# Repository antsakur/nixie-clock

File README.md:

# Nixie clock

ESP-IDF firmware for a four-tube HH:MM nixie clock on an ESP32-C6. The clock gets the time from SNTP over Wi-Fi, drives the tubes through shift registers, and serves a web page for setup and settings.

## Contents

- [What it does](#what-it-does)
- [How to use it](#how-to-use-it)
  - [First start](#first-start)
  - [Configuration](#configuration)
- [Functionality](#functionality)
  - [Display](#display)
    - [Clock](#clock)
    - [Cathode poisoning prevention routine](#cathode-poisoning-prevention-routine)
    - [Random digits](#random-digits)
  - [Brightness](#brightness)
  - [Presence](#presence)
  - [Time](#time)
  - [Network](#network)
- [How the hardware works](#how-the-hardware-works)
  - [Tubes](#tubes)
  - [Shift registers](#shift-registers)
  - [High-voltage supply](#high-voltage-supply)
  - [Presence sensor](#presence-sensor)
- [Build and flash](#build-and-flash)
- [Supported hardware](#supported-hardware)

## What it does

- Shows hours and minutes on four nixie tubes.
- Joins your saved Wi-Fi network and sets the clock from SNTP.
- Opens a setup network when it has no saved network, or when it cannot join.
- Can dim the tubes during night hours, and can turn the high-voltage supply off when nobody is nearby.
- Rolls the digits on a timer to reduce cathode poisoning.
- Crossfades digit changes when that effect is enabled.

Wi-Fi credentials are entered in the browser and stored on the clock.

## How to use it

### First start

1. Power the board from a 5 V supply that can provide 2 A, for example a USB phone charger. A 1 A supply may be insufficient. It opens a setup network named `NixieClock-XXXX`.
2. Join that network and open `http://nixie.local/`. If the name does not resolve, open `http://192.168.4.1/`.
3. Enter your SSID and password, then press **Join**. Tick **Hidden network** if the network is not advertised.
4. To access the configuration page, disconnect from the `NixieClock-XXXX` network, reconnect to your network, and open `http://nixie.local/` again.

### Configuration

On your network, `http://nixie.local/` opens five menus. Each **Save settings** button stores that menu on the clock, and the values stay after a reboot.

| Menu | What you can change |
|---|---|
| Display | Fade, cathode-poisoning routine, and random digits |
| Brightness | Day and night levels, night hours, and the transition between them |
| Presence | Idle timeout that turns the tubes off |
| Time | Timezone and daylight saving |
| Network | Connection details, and forgetting the saved network |

**Forget current network** on the Network page clears the saved credentials and returns the clock to the setup network.

## Functionality

The pictures are the pages from a configured clock. The values in them are that clock's saved settings, not the defaults described here.

### Display

#### Clock

The clock normally shows the current time. When fade is enabled, a digit change crossfades from the old digits to the new ones. Fade duration is how long that crossfade takes. The default is 500 ms, and it can be set from 1 ms to 5000 ms. **Test fade** fades every digit back and forth using the fade duration that is currently set. **Show clock** returns to the time.

<figure class="clip">

<figcaption><strong>All digits fading.</strong> Each tube crossfades to another digit and back, using the current fade duration.</figcaption>
</figure>

#### Cathode poisoning prevention routine

A nixie tube lights one cathode, the shaped digit, inside a gas-filled envelope. Metal slowly leaves the lit cathode and can settle on cathodes that stay dark. A clock repeats the same digits for long stretches, so unused digits grow dim, patchy, or fail to light. The routine walks every symbol on each tube so every cathode is lit regularly and that deposit does not build up.

You set the hold time for each digit, the starting offset, the run length, and whether it counts down. **Repeat every** is how many minutes pass between automatic runs. The default is 5 minutes. **Run cathode poisoning prevention routine** starts one run immediately.

<figure class="clip">

<figcaption><strong>Cathode poisoning prevention.</strong> The tubes walk through every symbol so each cathode is lit.</figcaption>
</figure>

#### Random digits

Random digits shows a changing pattern instead of the time. You set the hold time and how long the pattern runs. **Run random** starts it.

<figure class="clip">

<figcaption><strong>Random digits.</strong> The tubes show a changing pattern instead of the time.</figcaption>
</figure>

### Brightness

Tube brightness is controlled with PWM. The brightness number is the PWM duty-cycle, from 0 to 100. The defaults are 80 during the day and 60 at night. Night mode is off by default. When it is on, it runs from a start hour until an end hour and may cross midnight. The default night hours are 23:00 to 07:00. **Transition** is how many seconds the brightness takes to move between those levels, from 1 to 60. The default is 10 seconds. **Test transition** runs one change between the day and night levels.

A brightness of 0 turns the high-voltage supply off.

<figure class="clip">

<figcaption><strong>Brightness from full to off.</strong> The tubes dim from duty-cycle 100 to 0, then return to 100.</figcaption>
</figure>

### Presence

With the presence sensor enabled, the tubes turn off after the set number of minutes with nobody nearby. The default is 10 minutes. The allowed range is 1 to 240 minutes. Turning the sensor off leaves the tubes on, aside from a zero brightness setting.

### Time

Choose a timezone from the built-in list. Zones that observe daylight saving have a **Daylight saving** checkbox. The page shows the current clock time and the two SNTP servers compiled into the firmware. The defaults are `pool.ntp.org` and `time.google.com`.

The list covers UTC, the United Kingdom, Central and Eastern Europe, Finland, Moscow, India, China, Japan, Australia Eastern, and the four continental US zones.

### Network

The Network page shows the connected network, assigned IP address, firmware version, MAC address, and uptime. **Forget current network** erases the saved Wi-Fi credentials and starts the setup network again.

## How the hardware works

The clock is two boards. The lower board makes 170 V from the 5 V input and carries the presence sensor. The upper board holds four IN-14 nixie tubes and the shift registers that select their digits. An ESP32-C6 development kit is the controller. It gets the time over Wi-Fi and drives the shift registers, the tube brightness, and the high-voltage enable pin.

The high-voltage wiring can sit at 170 V while the clock is on. Do not touch that circuitry while it is powered.

### Tubes

Each IN-14 is a gas-filled tube with one common anode and a separate cathode for every symbol. About 170 V between the anode and a cathode ionizes the gas, and the glow takes the shape of that cathode. After the tube has struck, it keeps glowing at a lower voltage, about 145 V. The tube then looks like a short circuit, so each anode has a 13 kΩ resistor that holds the digit current to a few milliamps.

Each tube has cathodes for digits 0–9 and for a left and a right decimal point.

### Shift registers

Six TPIC6B595 shift registers are chained together. Each one has eight open-drain outputs that can pull a cathode to ground. An output that is on lights that cathode. An output that is off leaves it dark. The chain is 48 bits, sent least significant bit first:

| Bits | Tube |
|---|---|
| 47–36 | Hour tens |
| 35–24 | Hour ones |
| 23–12 | Minute tens |
| 11–0 | Minute ones |

Each group of 12 bits is one tube, in this order: left dot, digits 1 through 9, digit 0, right dot.

The controller sends serial data and a clock, then pulses the latch so all six registers update together. Output enable is a PWM signal. Its duty-cycle is the brightness number on the configuration page. The shift registers run from 5 V. Their outputs are clamped so they can sit at the tube voltage when a cathode is off.

### High-voltage supply

A flyback converter raises 5 V to 170 V for the tube anodes. An LT3757 controls the switch. The transformer is a Würth 750032051, with a 1:10 turns ratio so the switch duty-cycle stays in a practical range at 200 kHz. A BSC059N04LS6 MOSFET switches the primary. A VS-3EMH06 diode rectifies the secondary. An RCD snubber clamps the voltage spike on the MOSFET when it turns off. The converter is designed for about 20 mA at 170 V, which is enough for the four tubes. One GPIO enables the converter. Turning that pin off removes the anode voltage and the tubes go dark.

### Presence sensor

An HLK-LD2420 24 GHz radar module watches for a person nearby. It was chosen instead of a passive infrared sensor because it still sees someone who is sitting still. The clock only uses the module's presence output. A high level means someone is nearby, and a low level means the area is empty. When that output stays empty for the configured number of minutes, the firmware turns the high-voltage supply off.

## Build and flash

You need ESP-IDF 6.x. The target is `esp32c6`.

```bash
idf.py set-target esp32c6
idf.py menuconfig   # User Configuration: board and SNTP servers
idf.py build
idf.py -p /dev/ttyUSB0 flash monitor
```

In **User Configuration**:

- **Board** selects the DevKit pin map. The default is `ESP32_C6_WROOM_1`.
- **SNTP server** and **Backup SNTP server** are the only time servers the clock uses.
- **Initial connection retry count** is how many station disconnects to tolerate before giving up on credentials that have not yet received an IP, and before bringing the setup network back after a later disconnect. The default is 5.

Flash through the USB-UART bridge. The commands above use `/dev/ttyUSB0`.

## Supported hardware

| Board | Module | menuconfig |
|---|---|---|
| ESP32-C6-DevKitC-1 | ESP32-C6-WROOM-1 | `ESP32_C6_WROOM_1` (default) |
| ESP32-C6-DevKitM-1 | ESP32-C6-MINI-1 | `ESP32_C6_MINI_1` |

The firmware also expects:

- Four nixie tubes driven by shift registers (latch, data, and clock).
- A high-voltage supply with an enable pin.
- A PWM output-enable line for tube brightness.
- A presence sensor input.

Choosing the wrong board in menuconfig drives the high-voltage enable and the shift-register pins on the wrong GPIOs. The pin map for both kits is in [docs/esp32-c6-devkits.md](docs/esp32-c6-devkits.md).

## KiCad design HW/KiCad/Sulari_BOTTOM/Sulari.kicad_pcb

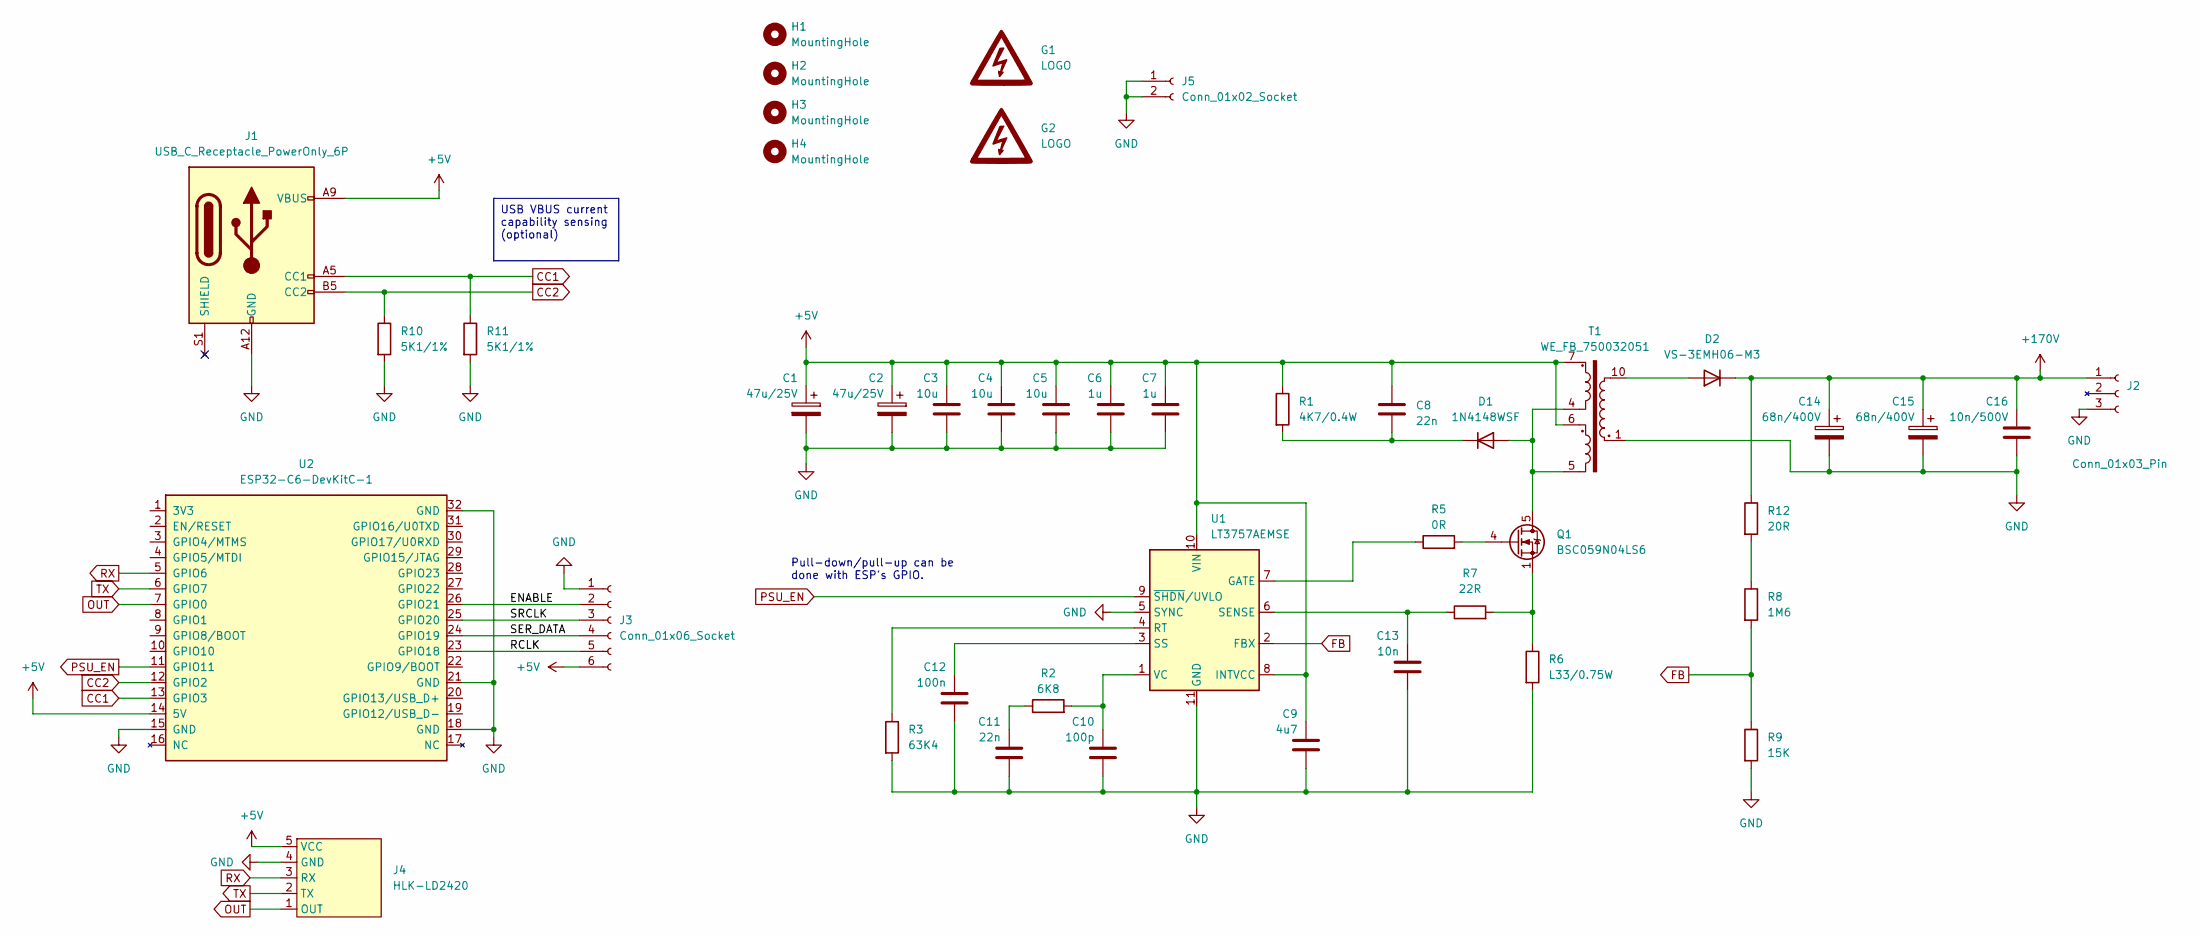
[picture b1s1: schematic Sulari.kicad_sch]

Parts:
C1, C2: 47u/25V; CP_Radial_D8.0mm_P3.50mm
C3, C4, C5: 10u; C_1206_3216Metric
C6, C7: 1u; C_0805_2012Metric
C8, C11: 22n; C_0603_1608Metric
C9: 4u7; C_0805_2012Metric
C10: 100p; C_0603_1608Metric
C12: 100n; C_0603_1608Metric
C13: 10n; C_0603_1608Metric
C14, C15: 68n/400V; C_Rect_L10.3mm_W5.0mm_P7.50mm_MKS4
C16: 10n/500V; C_1206_3216Metric_Pad1.33x1.80mm_HandSolder
D1: 1N4148WSF; D_SOD-323F
D2: VS-3EMH06-M3; D_SMA
G1, G2: LOGO; HIGH_VOLTAGE_LOGO
H1, H2, H3, H4: MountingHole; MountingHole_3.2mm_M3_Pad_Via
J1: USB_C_Receptacle_PowerOnly_6P; USB_C_Receptacle_GCT_USB4125-xx-x-0190_6P_TopMnt_Horizontal
J2: Conn_01x03_Pin; PinSocket_1x03_P2.54mm_Vertical
J3: Conn_01x06_Socket; PinSocket_1x06_P2.54mm_Vertical
J4: HLK-LD2420; Molex_PicoBlade_53048-0510_1x05_P1.25mm_Horizontal
J5: Conn_01x02_Socket; PinSocket_1x02_P2.54mm_Vertical
Q1: BSC059N04LS6; PG-TDSON-8-FL_correct
R1: 4K7/0.4W; R_0805_2012Metric
R2: 6K8; R_0603_1608Metric
R3: 63K4; R_0603_1608Metric
R5: 0R; R_0805_2012Metric_Pad1.20x1.40mm_HandSolder
R6: L33/0.75W; R_0805_2012Metric
R7: 22R; R_0603_1608Metric
R8: 1M6; R_1206_3216Metric
R9: 15K; R_0603_1608Metric
R10, R11: 5K1/1%; R_0805_2012Metric
R12: 20R; R_1206_3216Metric_Pad1.30x1.75mm_HandSolder
T1: WE_FB_750032051; WE_FB 750032051
U1: LT3757AEMSE; MSOP-10-1EP_3x3mm_P0.5mm_EP1.68x1.88mm_ThermalVias
U2: ESP32-C6-DevKitC-1

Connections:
+5V: C1.1, C2.1, C3.1, C4.1, C5.1, C6.1, C7.1, C8.1, C9.1, J1.A9 (VBUS), J1.B9 (VBUS), J3.6, J4.5 (VCC), R1.1, T1.6, T1.7, U1.8 (INTVCC), U1.10 (VIN), U2.14 (5V)
+170V: C14.1, C15.1, C16.1, D2.1 (K), J2.1, R12.1
/ENABLE: J3.2, U2.26 (GPIO21)
/RCLK: J3.5, U2.23 (GPIO18)
/SER_DATA: J3.4, U2.24 (GPIO19)
/SRCLK: J3.3, U2.25 (GPIO20)
CC1: J1.A5 (CC1), R11.1, U2.13 (GPIO3)
CC2: J1.B5 (CC2), R10.1, U2.12 (GPIO2)
FB: R8.2, R9.1, U1.2 (FBX)
GND: C1.2, C2.2, C3.2, C4.2, C5.2, C6.2, C7.2, C9.2, C10.2, C11.2, C12.2, C13.2, C14.2, C15.2, C16.2, J1.A12 (GND), J1.B12 (GND), J2.3, J3.1, J4.4 (GND), J5.1, J5.2, R3.2, R6.2, R9.2, R10.2, R11.2, T1.1, U1.5 (SYNC), U1.11 (GND), U2.15 (GND), U2.18 (GND), U2.21 (GND), U2.32 (GND)
unnamed: C11.1, R2.1
unnamed: D1.2 (A), Q1.5 (D), T1.4, T1.5
unnamed: C8.2, D1.1 (K), R1.2
unnamed: D2.2 (A), T1.10
unnamed: Q1.4 (G), R5.2
unnamed: Q1.1 (S), R6.1, R7.2
unnamed: R8.1, R12.2
unnamed: R5.1, U1.7 (GATE)
unnamed: R3.1, U1.4 (RT)
unnamed: C13.1, R7.1, U1.6 (SENSE)
unnamed: C12.1, U1.3 (SS)
unnamed: C10.1, R2.2, U1.1 (VC)
OUT: J4.1 (OUT), U2.7 (GPIO0)
PSU_EN: U1.9 (~SHDN/UVLO), U2.11 (GPIO11)
RX: J4.3 (RX), U2.5 (GPIO6)
TX: J4.2 (TX), U2.6 (GPIO7)

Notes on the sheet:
USB VBUS current capability sensing (optional)
Pull-down/pull-up can be done with ESP's GPIO.

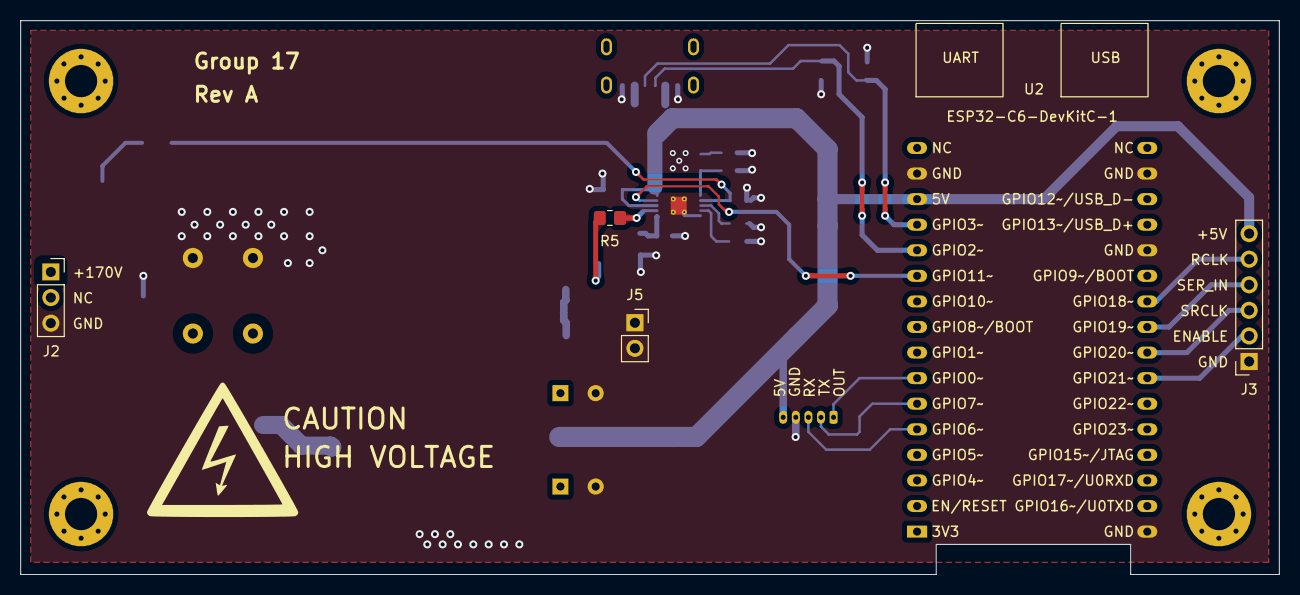
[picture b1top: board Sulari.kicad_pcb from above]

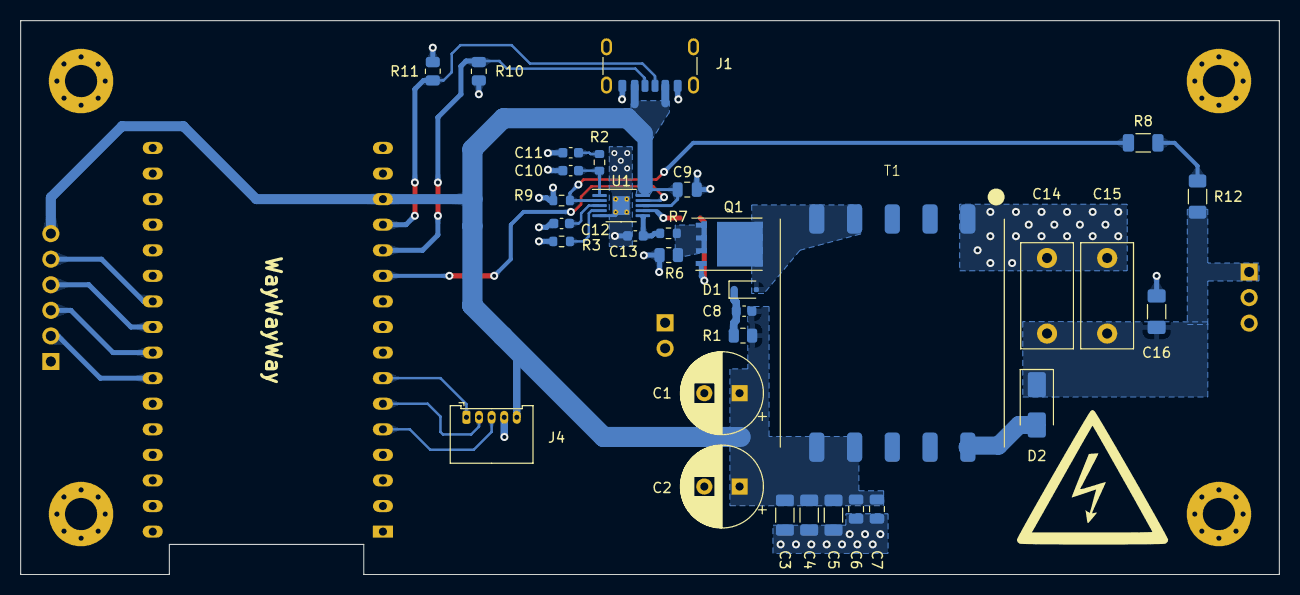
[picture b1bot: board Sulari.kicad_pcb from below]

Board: 2 copper layers, 125.0 x 55.0 mm, 44 parts (34 on the bottom side), 26 nets.

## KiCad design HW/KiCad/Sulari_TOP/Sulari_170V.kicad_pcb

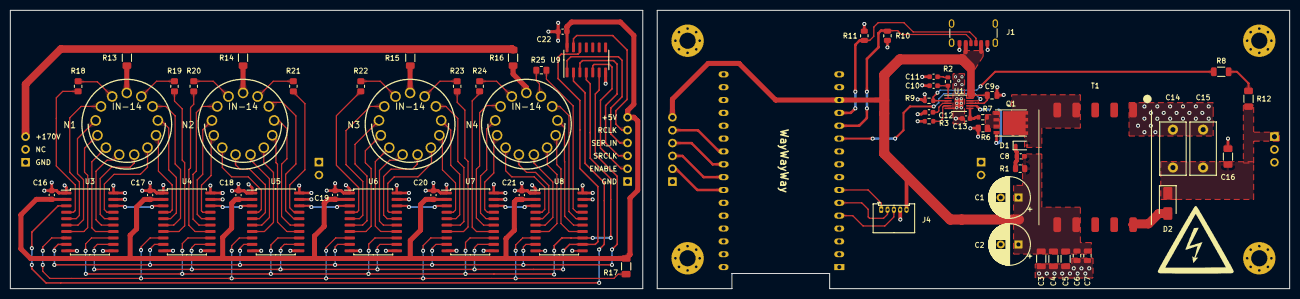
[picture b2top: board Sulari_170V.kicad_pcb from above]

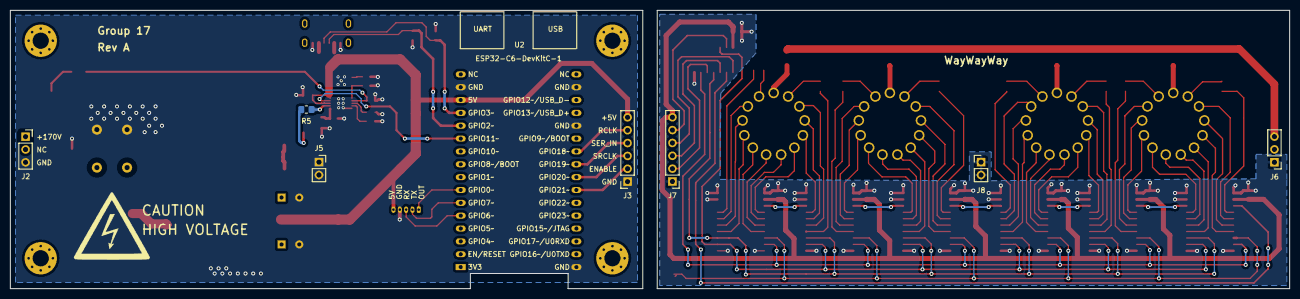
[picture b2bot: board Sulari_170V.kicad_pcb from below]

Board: 2 copper layers, 252.9 x 55.0 mm, 78 parts (13 on the bottom side), 101 nets.

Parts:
C1, C2: 47u/25V; CP_Radial_D8.0mm_P3.50mm
C3, C4, C5: 10u; C_1206_3216Metric
C6, C7: 1u; C_0805_2012Metric
C8, C11: 22n; C_0603_1608Metric
C9: 4u7; C_0805_2012Metric
C10: 100p; C_0603_1608Metric
C12: 100n; C_0603_1608Metric
C13: 10n; C_0603_1608Metric
C14, C15: 68n/400V; C_Rect_L10.3mm_W5.0mm_P7.50mm_MKS4
C16, C17, C18, C19, C20, C21, C22: 100n; C_0603_1608Metric_Pad1.08x0.95mm_HandSolder
C16#2: 10n/500V; C_1206_3216Metric_Pad1.33x1.80mm_HandSolder
D1: 1N4148WSF; D_SOD-323F
D2: VS-3EMH06-M3; D_SMA
G1, G2: LOGO; HIGH_VOLTAGE_LOGO
H1, H2, H3, H4: MountingHole; MountingHole_3.2mm_M3_Pad_Via
J1: USB_C_Receptacle_PowerOnly_6P; USB_C_Receptacle_GCT_USB4125-xx-x-0190_6P_TopMnt_Horizontal
J2: Conn_01x03_Pin; PinSocket_1x03_P2.54mm_Vertical
J3: Conn_01x06_Socket; PinSocket_1x06_P2.54mm_Vertical
J4: HLK-LD2420; Molex_PicoBlade_53048-0510_1x05_P1.25mm_Horizontal
J5: Conn_01x02_Socket; PinSocket_1x02_P2.54mm_Vertical
J6: Conn_01x03; PinHeader_1x03_P2.54mm_Vertical
J7: Conn_01x06; PinHeader_1x06_P2.54mm_Vertical
J8: Conn_01x02; PinHeader_1x02_P2.54mm_Vertical
N1, N2, N3, N4: IN-14; nixies-us-IN-14-socket
Q1: BSC059N04LS6; PG-TDSON-8-FL
R1: 4K7/0.4W; R_0805_2012Metric
R2: 6K8; R_0603_1608Metric
R3: 63K4; R_0603_1608Metric
R5: 0R; R_0805_2012Metric_Pad1.20x1.40mm_HandSolder
R6: L33/0.75W; R_0805_2012Metric
R7: 22R; R_0603_1608Metric
R8: 1M6; R_1206_3216Metric
R9: 15K; R_0603_1608Metric
R10, R11: 5K1/1%; R_0805_2012Metric
R12: 20R; R_1206_3216Metric_Pad1.30x1.75mm_HandSolder
R13, R14, R15, R16, R17: 13K; R_1206_3216Metric_Pad1.30x1.75mm_HandSolder
R18, R19, R20, R21, R22, R23, R24, R25: 100k; R_0805_2012Metric_Pad1.20x1.40mm_HandSolder
T1: WE_FB_750032051; WE_FB 750032051
U1: LT3757AEMSE; MSOP-10-1EP_3x3mm_P0.5mm_EP1.68x1.88mm
U2: ESP32-C6-DevKitC-1
U3, U4, U5, U6, U7, U8: TPIC6B595; SOIC-20W_7.5x12.8mm_P1.27mm
U9: SN74HCT04, 6-ch 5V logic inverter; SOIC-14_3.9x8.7mm_P1.27mm

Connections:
+5V: C1.1, C2.1, C3.1, C4.1, C5.1, C6.1, C7.1, C8.1, C9.1, C16.1, C17.1, C18.1, C19.1, C20.1, C21.1, C22.1, J1.A9 (VBUS), J1.B9 (VBUS), J3.6, J4.5 (VCC), J7.6, R1.1, R17.1, T1.6, T1.7, U1.8 (INTVCC), U1.10 (VIN), U2.14 (5V), U3.2 (VCC), U4.2 (VCC), U5.2 (VCC), U6.2 (VCC), U7.2 (VCC), U8.2 (VCC), U9.14
+170V: C14.1, C15.1, C16#2.1, D2.1 (K), J2.1, R12.1
/ENABLE: J3.2, U2.26 (GPIO21)
/RCLK: J3.5, U2.23 (GPIO18)
/SER_DATA: J3.4, U2.24 (GPIO19)
/SRCLK: J3.3, U2.25 (GPIO20)
/VDD_170V: J6.3, R13.1, R14.1, R15.1, R16.1
/~SRCLR: R17.2, U3.8 (~SRCLR), U4.8 (~SRCLR), U5.8 (~SRCLR), U6.8 (~SRCLR), U7.8 (~SRCLR), U8.8 (~SRCLR)
CC1: J1.A5 (CC1), R11.1, U2.13 (GPIO3)
CC2: J1.B5 (CC2), R10.1, U2.12 (GPIO2)
ENABLE: J7.2, U9.5
FB: R8.2, R9.1, U1.2 (FBX)
GND: C1.2, C2.2, C3.2, C4.2, C5.2, C6.2, C7.2, C9.2, C10.2, C11.2, C12.2, C13.2, C14.2, C15.2, C16.2, C16#2.2, C17.2, C18.2, C19.2, C20.2, C21.2, C22.2, J1.A12 (GND), J1.B12 (GND), J2.3, J3.1, J4.4 (GND), J5.1, J5.2, J6.1, J7.1, J8.1, J8.2, R3.2, R6.2, R9.2, R10.2, R11.2, T1.1, U1.5 (SYNC), U1.11 (GND), U2.15 (GND), U2.18 (GND), U2.21 (GND), U2.32 (GND), U3.1 (PGND), U3.10 (PGND), U3.11 (PGND), U3.19 (LGND), U3.20 (PGND), U4.1 (PGND), U4.10 (PGND), U4.11 (PGND), U4.19 (LGND), U4.20 (PGND), U5.1 (PGND), U5.10 (PGND), U5.11 (PGND), U5.19 (LGND), U5.20 (PGND), U6.1 (PGND), U6.10 (PGND), U6.11 (PGND), U6.19 (LGND), U6.20 (PGND), U7.1 (PGND), U7.10 (PGND), U7.11 (PGND), U7.19 (LGND), U7.20 (PGND), U8.1 (PGND), U8.10 (PGND), U8.11 (PGND), U8.19 (LGND), U8.20 (PGND), U9.7
unnamed: C11.1, R2.1
unnamed: D1.2 (A), Q1.5 (D), T1.4, T1.5
unnamed: C8.2, D1.1 (K), R1.2
unnamed: D2.2 (A), T1.10
unnamed: N1.A, R13.2
unnamed: N1.LHDP, R18.2
unnamed: N1.RHDP, R19.1
unnamed: N2.A, R14.2
unnamed: N2.LHDP, R20.2
unnamed: N2.RHDP, R21.1
unnamed: N3.A, R15.2
unnamed: N3.LHDP, R22.2
unnamed: N3.RHDP, R23.1
unnamed: N4.A, R16.2
unnamed: N4.LHDP, R24.2
unnamed: N4.RHDP, R25.1
unnamed: Q1.4 (G), R5.2
unnamed: Q1.1 (S), R6.1, R7.2
unnamed: R8.1, R12.2
unnamed: R5.1, U1.7 (GATE)
unnamed: R3.1, U1.4 (RT)
unnamed: C13.1, R7.1, U1.6 (SENSE)
unnamed: C12.1, U1.3 (SS)
unnamed: C10.1, R2.2, U1.1 (VC)
unnamed: R18.1, U3.4 (DRAIN0)
unnamed: N1.1, U3.5 (DRAIN1)
unnamed: N1.2, U3.6 (DRAIN2)
unnamed: N1.3, U3.7 (DRAIN3)
unnamed: N1.4, U3.14 (DRAIN4)
unnamed: N1.5, U3.15 (DRAIN5)
unnamed: N1.6, U3.16 (DRAIN6)
unnamed: N1.7, U3.17 (DRAIN7)
unnamed: U3.18 (SER_OUT), U4.3 (SER_IN)
unnamed: N1.8, U4.4 (DRAIN0)
unnamed: N1.9, U4.5 (DRAIN1)
unnamed: N1.0, U4.6 (DRAIN2)
unnamed: R19.2, U4.7 (DRAIN3)
unnamed: R20.1, U4.14 (DRAIN4)
unnamed: N2.1, U4.15 (DRAIN5)
unnamed: N2.2, U4.16 (DRAIN6)
unnamed: N2.3, U4.17 (DRAIN7)
unnamed: U4.18 (SER_OUT), U5.3 (SER_IN)
unnamed: N2.4, U5.4 (DRAIN0)
unnamed: N2.5, U5.5 (DRAIN1)
unnamed: N2.6, U5.6 (DRAIN2)
unnamed: N2.7, U5.7 (DRAIN3)
unnamed: N2.8, U5.14 (DRAIN4)
unnamed: N2.9, U5.15 (DRAIN5)
unnamed: N2.0, U5.16 (DRAIN6)
unnamed: R21.2, U5.17 (DRAIN7)
unnamed: U5.18 (SER_OUT), U6.3 (SER_IN)
unnamed: R22.1, U6.4 (DRAIN0)
unnamed: N3.1, U6.5 (DRAIN1)
unnamed: N3.2, U6.6 (DRAIN2)
unnamed: N3.3, U6.7 (DRAIN3)
unnamed: N3.4, U6.14 (DRAIN4)
unnamed: N3.5, U6.15 (DRAIN5)
unnamed: N3.6, U6.16 (DRAIN6)
unnamed: N3.7, U6.17 (DRAIN7)
unnamed: U6.18 (SER_OUT), U7.3 (SER_IN)
unnamed: N3.8, U7.4 (DRAIN0)
unnamed: N3.9, U7.5 (DRAIN1)
unnamed: N3.0, U7.6 (DRAIN2)
unnamed: R23.2, U7.7 (DRAIN3)
unnamed: R24.1, U7.14 (DRAIN4)
unnamed: N4.1, U7.15 (DRAIN5)
unnamed: N4.2, U7.16 (DRAIN6)
unnamed: N4.3, U7.17 (DRAIN7)
unnamed: U7.18 (SER_OUT), U8.3 (SER_IN)
unnamed: N4.4, U8.4 (DRAIN0)
unnamed: N4.5, U8.5 (DRAIN1)
unnamed: N4.6, U8.6 (DRAIN2)
unnamed: N4.7, U8.7 (DRAIN3)
unnamed: N4.8, U8.14 (DRAIN4)
unnamed: N4.9, U8.15 (DRAIN5)
unnamed: N4.0, U8.16 (DRAIN6)
unnamed: R25.2, U8.17 (DRAIN7)
OUT: J4.1 (OUT), U2.7 (GPIO0)
PSU_EN: U1.9 (~SHDN/UVLO), U2.11 (GPIO11)
RCLK: J7.5, U9.13
RX: J4.3 (RX), U2.5 (GPIO6)
SER_IN: J7.4, U9.1
SRCLK: J7.3, U9.3
TX: J4.2 (TX), U2.6 (GPIO7)
~ENABLE: U3.9 (~G), U4.9 (~G), U5.9 (~G), U6.9 (~G), U7.9 (~G), U8.9 (~G), U9.6
~RCLK: U3.12 (RCLK), U4.12 (RCLK), U5.12 (RCLK), U6.12 (RCLK), U7.12 (RCLK), U8.12 (RCLK), U9.12
~SER_IN: U3.3 (SER_IN), U9.2
~SRCLK: U3.13 (SRCK), U4.13 (SRCK), U5.13 (SRCK), U6.13 (SRCK), U7.13 (SRCK), U8.13 (SRCK), U9.4

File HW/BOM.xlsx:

Item # | Qty |  | Ref Des | Manufacturer | Manf part num | Description | Footprint | Type | Digikey price/pc (€) | Total
 |  | Comment
 |  | Capacitors |  |  |  |  |  |  | excluding VAT
 | 1 | 100pF | C10 | Yageo | CC0603JRNPO9BN101 | Multilayer Ceramic Capacitor, 100 pF, 50 V, ± 5%, C0G (NP0), 0603 [1608 Metric] | 0603 | SMT | 0.09 | 0.09
 | 1 | 10nf, 500V, X7R | C16 | Wurth Elektronik | 885342208009 | Cap Cer 10000PF 500V X7R 1206 | 1206 | SMT | 0.12 | 0.12
 | 1 | 10nf | C13 | Murata | GCM188R72A103KA37D | Multilayer Ceramic Capacitor, 0.01 uF, 100 V, ± 10%, X7R, 0603 [1608 Metric] | 0603 | SMT | 0.09 | 0.09
 | 2 | 22nf, 100V | C8,C11 | Murata | GCM188R72A223KA37J | Multilayer Ceramic Capacitor, 0.022 uF, 100 V, ± 10%, X7R, 0603 [1608 Metric] | 0603 | SMT | 0.1 | 0.2
 | 2 | 68nf, 400V | C14, C15 | Wurth Elektronik | 890283422001CS | Cap, 0.068Uf, 400V, Film, Radial Rohs Compliant: Yes |Wurth Elektronik 89028342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 | WCAP-FTBE_L10.5xH11xP7.5 | THT | 0.44 | 0.88
 | 7 | 100nf, 16V | C12, C17-22 | Yageo | CC0603KRX7R7BB104 | Multilayer Ceramic Capacitor, 0.1 uF, 16 V, ± 10%, X7R, 0603 [1608 Metric] | 0603 | SMT | 3.9E-2 | 0.27300000000000002
 | 2 | 1uf, 25V, X7R | C6,C7 | Samsung | CL21B105KAFNNNE | Multilayer Ceramic Capacitor, 1 uF, 25 V, ± 10%, X7R, 0805 [2012 Metric] | 0805 | SMT | 0.09 | 0.18
 | 3 | 10uf, 25V, X7R | C3,C4,C5 | Samsung | CL31B106KAHNFNE | Multilayer Ceramic Capacitor, 10 uF, 25 V, ± 10%, X7R, 1206 [3216 Metric] | 1206 | SMT | 0.21 | 0.63
 | 1 | 47uF, 16V, X7R | C9 | Murata | GRM21BR71C475KE51L | Multilayer Ceramic Capacitor, 4.7 uF, 16 V, ± 10%, X7R, 0805 [2012 Metric] | 0805 | SMT | 0.14000000000000001 | 0.14000000000000001
 | 2 | 47uF, 25V | C1,C2 | Wurth Elektronik | 870025574002 | WCAP-PTG5 Aluminum Polymer Capacitors | WCAP-PTG5_D8xH8xP3.5 | THT | 0.68 | 1.36
 | 1 | 0 | R5 | Yageo | RC0805FR-070RL | Thick film chip resistor; smd; 0805; 0.00R; 0.125W; 1%; ; operating temperature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 | 0805 | SMT | 0.09 | 0.09
 | 1 | 2 | R5 | Yageo | RC0805FR-072RL | SMD Chip Resistor, 2 Ohm, ± 1%, 125 mW, 0805 [2012 Metric], Thick Film, General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 | 0805 | SMT | 0.09 | 0.09
 | 1 | 33m, 3/4W | R6 | Thin Film Tech | D1WEL0805MR033F-T5 | Res 0.033 Ohm 1% 3/4W 0805 | 0805 | SMT | 0.42 | 0.42
 | 1 | 20 | R12 | Yageo | RC1206JR-0720RL | SMD Chip Resistor, 20 Ohm, ± 5%, 250 mW, 1206 [3216 Metric], Thick Film, Genera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 | 1206 | SMT | 0.09 | 0.09
 | 1 | 22 | R7 | Yageo | RC0603FR0722RL | SMD Chip Resistor, 22 Ohm, ± 1%, 100 mW, 0603 [1608 Metric], Thick Film, Genera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 | 0603 | SMT | 0.09 | 0.09
 | 1 | 4.7k, 0.4W | R1 | Vishay | RCS08054K70FKEA | Res Thick Film 0805 4.7K Ohm 1% 0.4W ±100ppm/°C Pad SMD Automotive Medical T/R | 0805 | SMT | 0.12 | 0.12
 | 2 | 5.1k, 1% | R10,R11 | Yageo | RC0805FR-075K1L | SMD Chip Resistor, 5.1 kOhm, ± 1%, 125 mW, 0805 [2012 Metric], Thick Film, Gene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 | 0805 | SMT | 0.09 | 0.18
 | 1 | 6.8k | R2 | Yageo | RC0603FR-076K8L | SMD Chip Resistor, 6.8 kOhm, ± 1%, 100 mW, 0603 [1608 Metric], Thick Film, Gene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 | 0603 | SMT | 0.09 | 0.09
 | 5 | 13k | R13-17 | KOA Speer | RK73B2BTTD133J | Res Thick Film 1206 13K Ohm 5% 0.25W(1/4W) ±200ppm/C Pad SMD Automotive T/R | 1206 | SMT | 0.03 | 0.15
 | 1 | 15k | R9 | Yageo | RC0603FR-0715KL | SMD Chip Resistor, 15 kOhm, ± 1%, 100 mW, 0603 [1608 Metric], Thick Film, Gener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 | 0603 | SMT | 0.09 | 0.09
 | 1 | 63.4k | R3 | Stackpole Electronics | RMCF0603FT63K4 | Res Thick Film 0603 63.4K Ohm 1% 1/10W ±100ppm/°C Molded SMD SMD Paper T/R | 0603 | SMT | 0.09 | 0.09
 | 8 | 100k | R18-R25 | Yageo | RC0805FR-07100KL |  | 0805 | SMT
 | 1 | 1.6M | R8 | Yageo | RC1206FR-071M6L | SMD Chip Resistor, 1.6 MOhm, ± 1%, 250 mW, 1206 [3216 Metric], Thick Film, Gene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 | 1206 | SMT | 0.09 | 0.09
 | 1 | 2A, 600V | D2 | Vishay | VS-3EMH06-M3/5AT | Diode Hyper Fast Recovery Rectifier 600V 3A 2-Pin DO-214AC Plastic T/R | SMA (DO-214AC) | SMT | 0.4 | 0.4
 | 1 | 0.25A, 100V | D1 | Diodes Inc. | 1N4148WSF-7 | Rectifier Diode Small Signal Switching 100V 0.25A 4ns 2-Pin SOD-323F T/R | SOD323F | SMT | 0.17 | 0.17
 | 1 | 40V | Q1 | Infineon | BSC059N04LS6 | OptiMO 6 40V power MOSFETs combining best-in-class RDS(on) with superior switch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 | TDSON-8 FL | SMT | 1.05 | 1.05
 | 1 | 10uH | T1 | Wurth Elektronik | 750032051 | Pulse Transformer, 1: 10, 10 H, 0.7 Ohm, 1 Kv | - | SMT | 4.68 | 4.68
 | 1 | LT3757A | U1 | Analog Devices | LT3757AEMSE#PBF | DC DC Cntrlr Single-OUT Flyback Controller 2.9V to 40V Input Automotive 10-Pin 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 | 10-TFSOP, 10-MSOP (0.118", 3.00mm Width) Exposed Pad | SMT | 6.15 | 6.15
 | 6 | TPIC6B595 | U3-U8 | Texas Instruments | TPIC6B595DWR | 8 Bit Sipo Shift Register, SOIC-20; Shif; Msl: Msl 1 - Unlimited; Svhc: No Svhc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 | 20-SOIC | SMT | 1.39 | 8.34
 | 1 | SN74HCT04 | U9 | Texas Instruments | SN74HCT04DR | 6-ch, 4.5-V to 5.5-V inverters with TTL-compatible CMOS inputs 14-SOIC -40 to 85 | 14-SOIC | SMT | 0.33 | 0.33
 | 1 | USB4125 | J1 | GCT | USB4125-GF-A-0190 | 24 (6+18 Dummy) Position USB-C (USB TYPE-C) USB 2.0 Receptacle Connector | USB 6P | THT | 0.62 | 0.62
 | 1 | 5POS 1.25mm | J4 | Molex | 0530480510 | Conn Shrouded Header (4 Sides) HDR 5 POS 1.25mm Solder RA Side Entry Thru-Hole 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 | 1x05_P1.25mm | THT | 0.45 | 0.45
 | 1 | 5POS 1.25mm | - | Molex | 0510210500 | MOLEX 51021-0500 1.25mm Pitch Housing Female 5p PicoBlade Wire-to-Wire +Wire-to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 | - | CONNECTOR | 0.24 | 0.24
 | 10 | 28-32AWG | - | Molex | 0500588000 | 1.25mm Pitch, PicoBlade Female Crimp Terminal, Tin (Sn) Plating, 28-32 AWG, Reel | - | CONNECTOR | 3.9E-2 | 0.39
 | 1 | 2POS socket | J5 | Sullins | PPPC021LFBN-RC | Female, 2 C, Straight .100" CC; 3.20mm Tail, No Mounting; PBT, Phos. Bronze, 10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 | 1x02_P2.54mm | THT | 0.31 | 0.31
 | 1 | 3POS socket | J2 | Sullins | PPPC031LFBN-RC | 3 Position Total Single Row 2.54 mm Pitch Straight Female Header | 1x03_P2.54mm | THT | 0.35 | 0.35
 | 1 | 6POS socket | J3 | Sullins | PPPC061LFBN-RC | 6 Position Header Connector 0.100 (2.54mm) Through Hole Gold" | 1x06_P2.54mm | THT | 0.5 | 0.5
 | 1 | 2POS header | J8 | Sullins | PREC002SAAN-RC | Automotive Connectors CLIP HSG FOR 090 II MLC | 1x02_P2.54mm | THT | 0.09 | 0.09
 | 1 | 3POS header | J6 | Sullins | PREC003SAAN-RC | Conn Header Vert 3POS 2.54MM | 1x03_P2.54mm | THT | 0.09 | 0.09
 | 1 | 6POS header | J7 | Sullins | PREC006SAAN-RC | Conn Header .100" Sngl Str 6POS | 1x06_P2.54mm | THT | 0.14000000000000001 | 0.14000000000000001
 | 60 | Tube socket |  | Preci-Dip | 01401-87-3010 | Pin Receptacle Connector 0.014" |  | THT | 8.7300000000000003E-2 | 5.2380000000000004
 | 1 | ESP32-C6 | U2 | Espressif | ESP32-C6-DEVKITC-1-N8 | Development Board WiFi, Bluetooth® 5, Flash 8MB | 2x15_P2.54mm | THT | 8.31 | 8.31
 | 2 | 15POS socket |  | Sullins | PPTC151LFBN-RC | Board Connector, 15 Contact(s), 1 Row(s), Female, Straight, 0.1 inch Pitch, Sol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 | 2x15_P2.54mm | THT | 0.91 | 1.82
 | 4 | 970150321 |  | Wurth Elektronik | 970150321 | WA-SSTII Steel Spacer Stud Metric Thread int./int. | M3x0.5 15mm |  | 0.34 | 1.36
 | 4 | 50M030050P008 |  | Essentra | 50M030050P008 | Pan Phillips Screw, M3 X .5 Thread, 8MM Lg | Essentra Components 50M030050P008 | M3x0.5 8mm |  | 0.12 | 0.48
 |  |  |  |  |  |  |  |  | Total w/o VAT | 45.221000000000004
 |  |  |  |  |  |  |  |  | TOTAL VAT 24% | 56.074040000000004

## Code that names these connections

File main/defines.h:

#if CONFIG_ESP32_C6_WROOM_1
    #define GPIO_PRESENCE_SENSOR GPIO_NUM_0
    #define GPIO_VBUS_CC2        GPIO_NUM_1
    #define GPIO_VBUS_CC1        GPIO_NUM_2
    #define GPIO_UART_RX         GPIO_NUM_6
    #define GPIO_UART_TX         GPIO_NUM_7
    #define GPIO_PSU_EN          GPIO_NUM_11
    #define GPIO_RCLK            GPIO_NUM_18
    #define GPIO_SRDATA          GPIO_NUM_19
    #define GPIO_SRCLK           GPIO_NUM_20
    #define GPIO_OUTPUT_EN       GPIO_NUM_21
#elif CONFIG_ESP32_C6_MINI_1
    #define GPIO_PRESENCE_SENSOR GPIO_NUM_0
    //#define GPIO_VBUS_CC2        GPIO_NUM_
    //#define GPIO_VBUS_CC1        GPIO_NUM_
    #define GPIO_UART_RX         GPIO_NUM_4
    #define GPIO_UART_TX         GPIO_NUM_5
    #define GPIO_PSU_EN          GPIO_NUM_7
    #define GPIO_RCLK            GPIO_NUM_15
    #define GPIO_SRDATA          GPIO_NUM_18
    #define GPIO_SRCLK           GPIO_NUM_19
    #define GPIO_OUTPUT_EN       GPIO_NUM_20
#endif

#define RMT_RESOLUTION_HZ 1000000 // 1MHZ, 1 tick = 1us

#define PWM_RESOLUTION_BITS 10    // PWM duty-cycle resolution is 0-1024

#define ENABLE  1
#define DISABLE 0

#define ESP_INTR_FLAG_DEFAULT 0

#define WIFI_CONNECTED_BIT BIT0
#define WIFI_FAIL_BIT      BIT1

#define TIMER_UPDATE_DISP 1
#define TIMER_ROLL_DISP   2
#define TIMER_NO_MOVEMENT 3

#define WIFI_SUCCESS 1
#define WIFI_FAILURE 2

#define MAIN_TASK_SETUP_DONE 1
#define ANIMATION_TASK_DONE  2

#define ESP_WIFI_SSID           CONFIG_ESP_WIFI_SSID
#define ESP_WIFI_PASS           CONFIG_ESP_WIFI_PASSWORD
#define ESP_MAXIMUM_RETRY       CONFIG_ESP_MAXIMUM_RETRY

#define SNTP_TIME_SERVER        CONFIG_SNTP_TIME_SERVER

#if CONFIG_ESP_WIFI_AUTH_OPEN
#define ESP_WIFI_SCAN_AUTH_MODE_THRESHOLD WIFI_AUTH_OPEN
#elif CONFIG_ESP_WIFI_AUTH_WEP
#define ESP_WIFI_SCAN_AUTH_MODE_THRESHOLD WIFI_AUTH_WEP
#elif CONFIG_ESP_WIFI_AUTH_WPA_PSK
#define ESP_WIFI_SCAN_AUTH_MODE_THRESHOLD WIFI_AUTH_WPA_PSK
#elif CONFIG_ESP_WIFI_AUTH_WPA2_PSK
#define ESP_WIFI_SCAN_AUTH_MODE_THRESHOLD WIFI_AUTH_WPA2_PSK
#elif CONFIG_ESP_WIFI_AUTH_WPA_WPA2_PSK
#define ESP_WIFI_SCAN_AUTH_MODE_THRESHOLD WIFI_AUTH_WPA_WPA2_PSK
#elif CONFIG_ESP_WIFI_AUTH_WPA3_PSK
#define ESP_WIFI_SCAN_AUTH_MODE_THRESHOLD WIFI_AUTH_WPA3_PSK
#elif CONFIG_ESP_WIFI_AUTH_WPA2_WPA3_PSK
#define ESP_WIFI_SCAN_AUTH_MODE_THRESHOLD WIFI_AUTH_WPA2_WPA3_PSK
#elif CONFIG_ESP_WIFI_AUTH_WAPI_PSK
#define ESP_WIFI_SCAN_AUTH_MODE_THRESHOLD WIFI_AUTH_WAPI_PSK
#endif

#if CONFIG_ESP_WPA3_SAE_PWE_HUNT_AND_PECK
#define ESP_WIFI_SAE_MODE WPA3_SAE_PWE_HUNT_AND_PECK
#define H2E_IDENTIFIER ""
#elif CONFIG_ESP_WPA3_SAE_PWE_HASH_TO_ELEMENT
#define ESP_WIFI_SAE_MODE WPA3_SAE_PWE_HASH_TO_ELEMENT
#define H2E_IDENTIFIER CONFIG_ESP_WIFI_PW_ID
#elif CONFIG_ESP_WPA3_SAE_PWE_BOTH
#define ESP_WIFI_SAE_MODE WPA3_SAE_PWE_BOTH
#define H2E_IDENTIFIER CONFIG_ESP_WIFI_PW_ID
#endif

#if CONFIG_BUILD_MAIN_PROGRAM
#define BUILD_MAIN_PROGRAM
#endif
